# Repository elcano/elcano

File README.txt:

Welcome to the Elcano autonomous tricycle project!
Please see:
http://www.elcanoproject.org/

This repository has been archived. The system consists of several different microprocessors. Elcano/Elcano has been broken into separate repositories for each processor.

To get started, fork and clone the repository:
https://github.com/elcano/elcano

Parameters and settings for each trike are defined in:
/libraries/Settings/Settings.h

Place the contents of the libraries folder into your libraries folder under
Arduino/libraries

The repository includes examples in the file:
Arduino/libraries/Settings/SettingsTemplate.h

Only libraries/Settings/SettingsTemplate.h should be committed in the
repository -- the Arduino/libraries/Settings/Settings.h file is site-specific.

-- Copy
   Arduino/libraries/Settings/SettingsTemplate.h
   to
   Arduino/libraries/Settings/Settings.h
-- Give your trike a different VEHICLE_NUMBER value.
-- Add your own trike's settings, following the examples.
-- Put your settings in a conditional for your new VEHICLE_NUMBER value.

When you pull in updates from the main repository, look for changes in
SettingsTemplate.h and if needed merge them with your own Settings.h.
Especially watch for new trike parameters used in sketches.

Sketches that need these settings should
#include <Settings.h>
*after* all other includes or definitions that are used in Settings.h.

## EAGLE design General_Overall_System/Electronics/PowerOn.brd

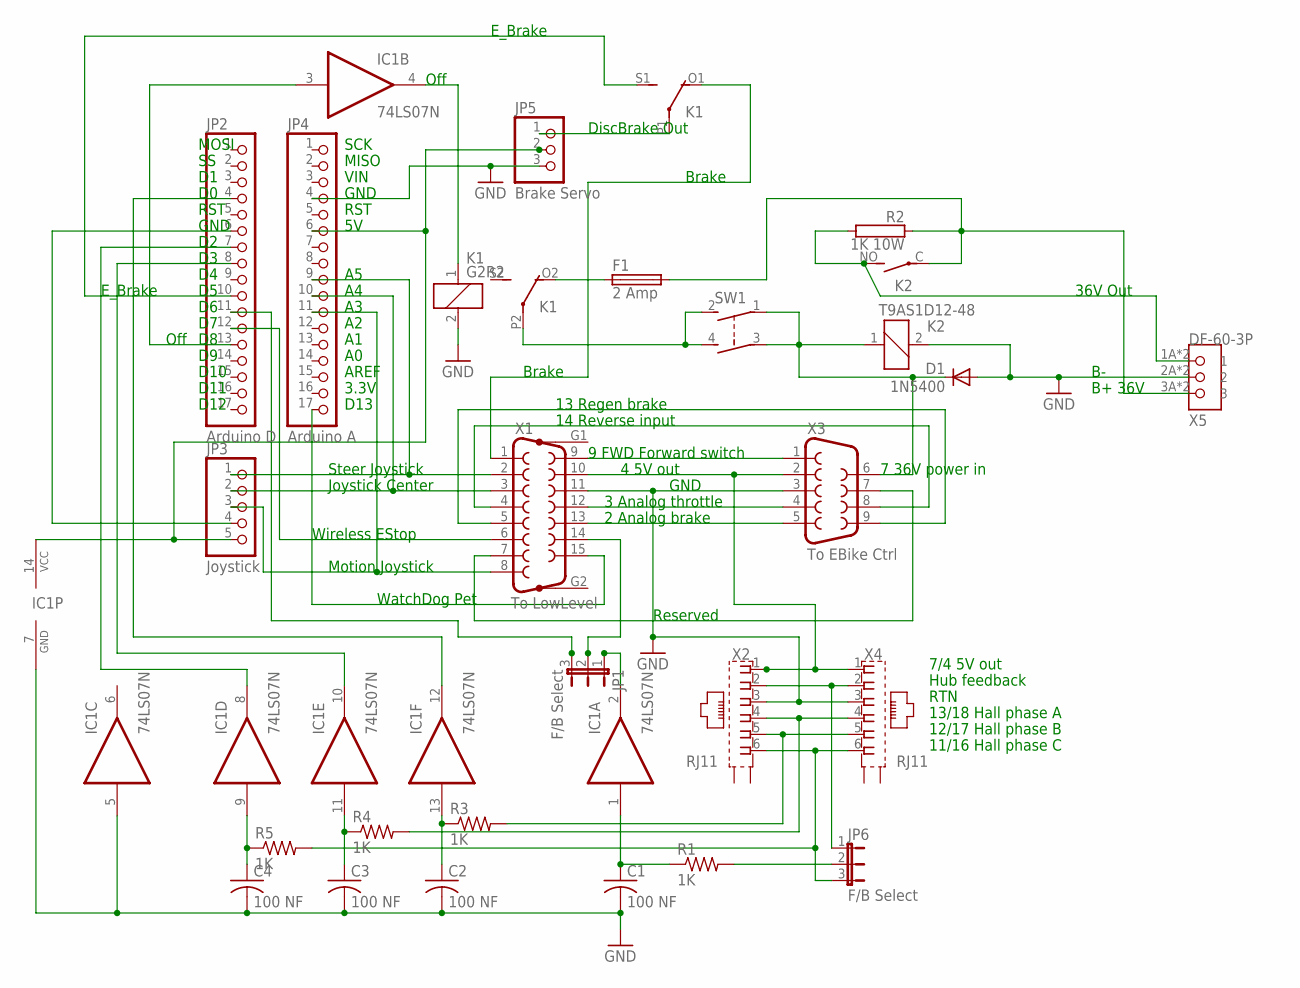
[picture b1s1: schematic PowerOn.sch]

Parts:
C1: 100 NF; C050-050X075
C2, C3, C4: 100 NF; C050-024X044
D1: 1N5400; DO201-15
F1: 2 Amp; SH22,5
IC1: 74LS07N; DIL14
JP1, JP6: F/B Select; JP2
JP2: Arduino D; 1X17
JP3: Joystick; 1X05/90
JP4: Arduino A; 1X17
JP5: Brake Servo; 1X03/90
K1: G2R2
K2: T9AS1D12-48; JT1A-PCB
R1: 1K; 0411/15
R2: 1K 10W; AC07
R3, R4, R5: 1K; 0207/10
SW1: CK-S201
X1: To LowLevel; F15HP
X2, X4: RJ11; XRJK-S-01-6-6-0-2G2-NO
X3: To EBike Ctrl; F09H
X5: HIROSE-DF60-3P-10.16DSA; DF-60-3P-10.16

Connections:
36V_BAT: F1.2, K2.C, R2.1, X5.3A (3), X5.3B (3)
36V_CL: D1.C, K2.1, SW1.1, SW1.3 (P1), X3.6
36V_OUT: K2.NO (S), R2.2, X5.1A (1), X5.1B (1)
36V_SW: K1.P2, SW1.2 (S), SW1.4 (S1)
BRAKE: K1.O1 (O), X1.1
BRK: X1.13, X3.5
BRK_OUT: JP5.1, K1.P1
EBRAKE: JP2.10, K1.S1 (S)
E_RQST: JP2.12, X1.6
F/B: JP1.2, X1.14
FB_SEL: JP6.2, R1.2
FWD: X1.9, X3.1
GND: C1.2, C2.2, C3.2, C4.2, D1.A, IC1.5 (I), IC1.7 (GND), JP4.4, JP5.3, K1.2, K2.2, X1.11, X2.3, X3.3, X4.3, X5.2A (2), X5.2B (2)
GND2: JP2.6, JP3.4
HALLA: R4.2, X2.4, X4.4
HALLB: R3.2, X2.5, X4.5
HALLC: JP6.3, R5.2, X2.6, X4.6
JOY_CEN: JP3.2, JP4.10, X1.3
JOY_MOT: JP3.3, JP4.11, X1.8
JOY_STR: JP3.1, JP4.9, X1.2
LIVE: X1.10, X2.1, X3.2, X4.1
unnamed: IC1.2 (O), JP1.1
unnamed: F1.1, K1.O2 (O)
unnamed: C2.1, IC1.13 (I), R3.1
unnamed: C3.1, IC1.11 (I), R4.1
unnamed: C4.1, IC1.9 (I), R5.1
unnamed: IC1.8 (O), JP2.7
unnamed: IC1.10 (O), JP2.8
unnamed: IC1.12 (O), JP2.4
unnamed: JP1.3, JP2.11
OFF: IC1.3 (I), JP2.13
OFF_DRV: IC1.4 (O), K1.1
RESERVE: X1.7, X3.7
REV: X1.4, X3.8
RGN: X1.5, X3.9
SPD: C1.1, IC1.1 (I), R1.1
SPEED: JP6.1, X2.2, X4.2
THROT: X1.12, X3.4
VCC: IC1.14 (VCC), JP3.5, JP4.6, JP5.2
WDOG: JP4.17, X1.15

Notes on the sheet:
7 36V power in
3 Analog throttle
2 Analog brake
13 Regen brake
14 Reverse input
RTN
13/18 Hall phase A
11/16 Hall phase C
12/17 Hall phase B
7/4 5V out
B+ 36V
Hub feedback
WatchDog Pet
DiscBrake Out
4 5V out
Wireless EStop
Steer Joystick
Joystick Center
Motion Joystick
D12
D11
D10
GND
RST
MOSI
MISO
D13
3.3V
AREF
VIN
SCK
Off
Brake
E_Brake
Reserved
9 FWD Forward switch
36V Out

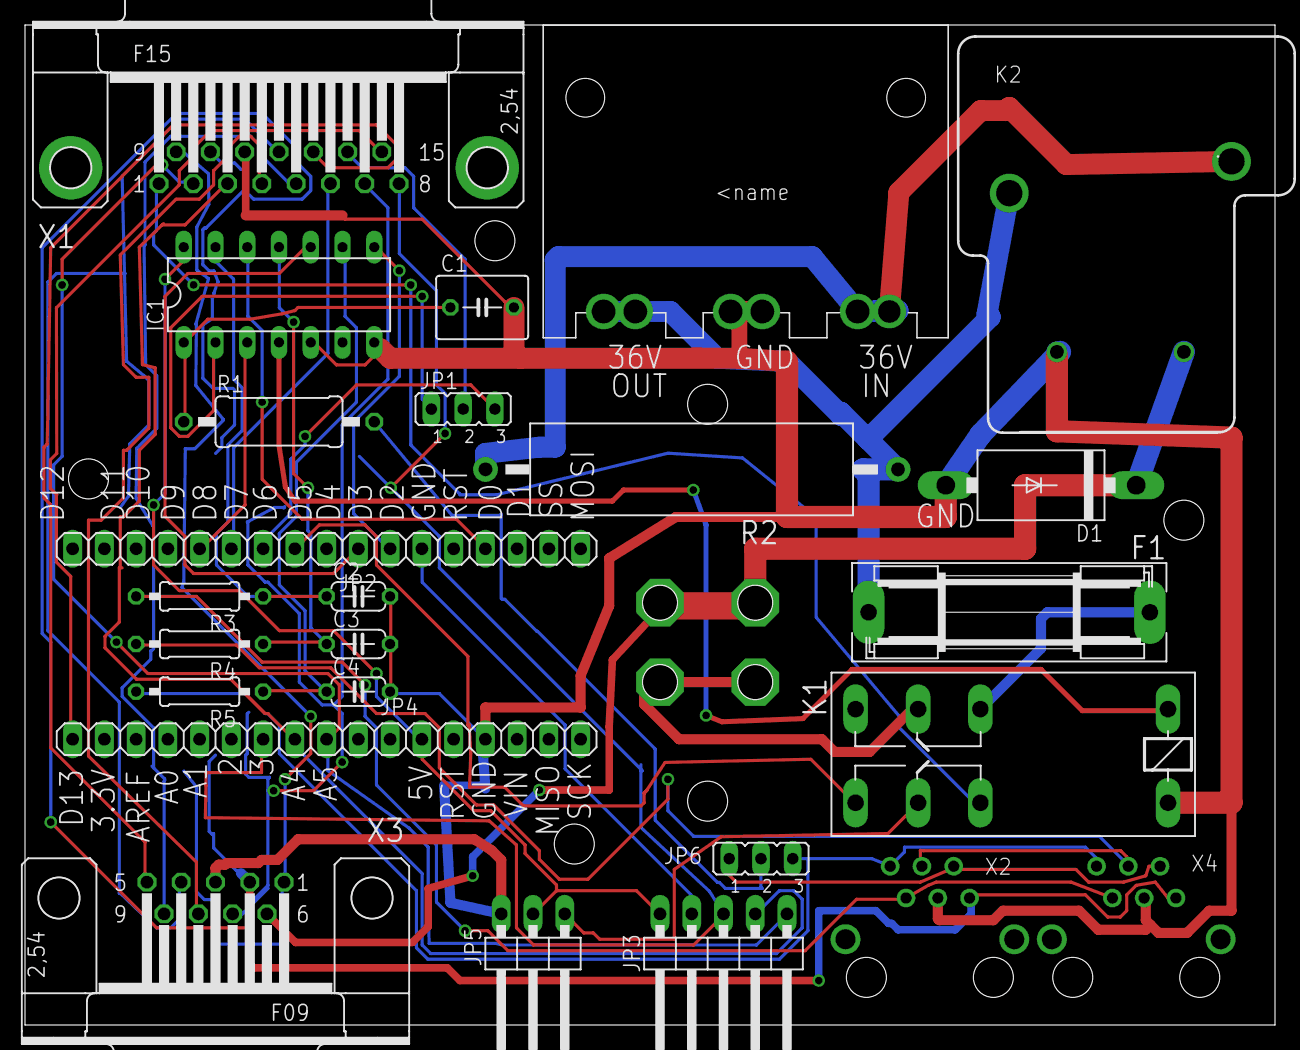
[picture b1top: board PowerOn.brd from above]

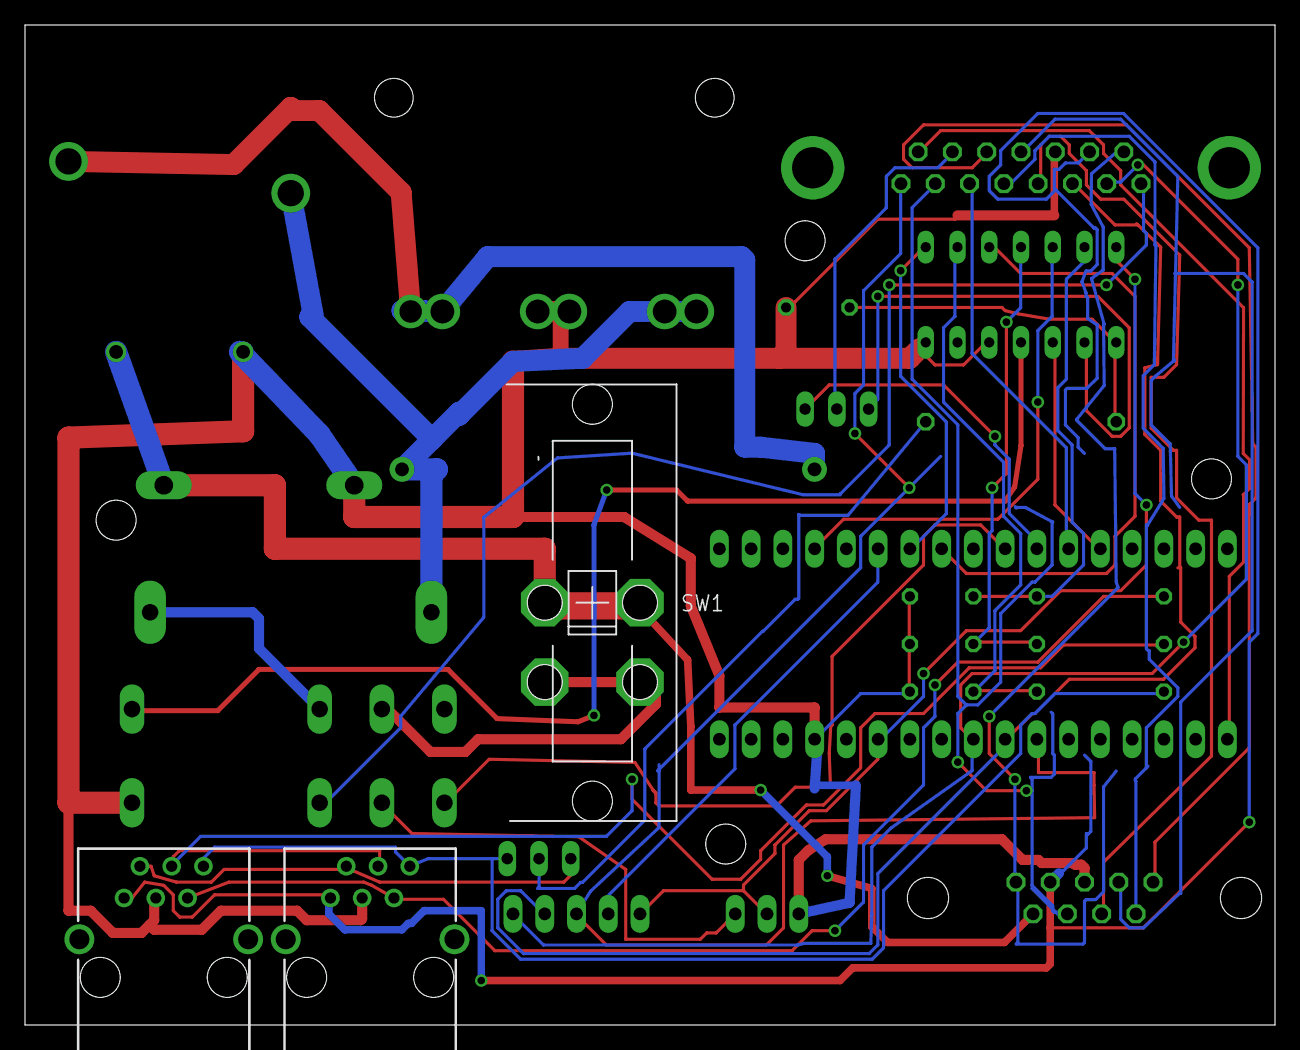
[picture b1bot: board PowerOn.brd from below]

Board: 2 copper layers, 100.0 x 80.0 mm, 26 parts (3 on the bottom side), 40 nets.

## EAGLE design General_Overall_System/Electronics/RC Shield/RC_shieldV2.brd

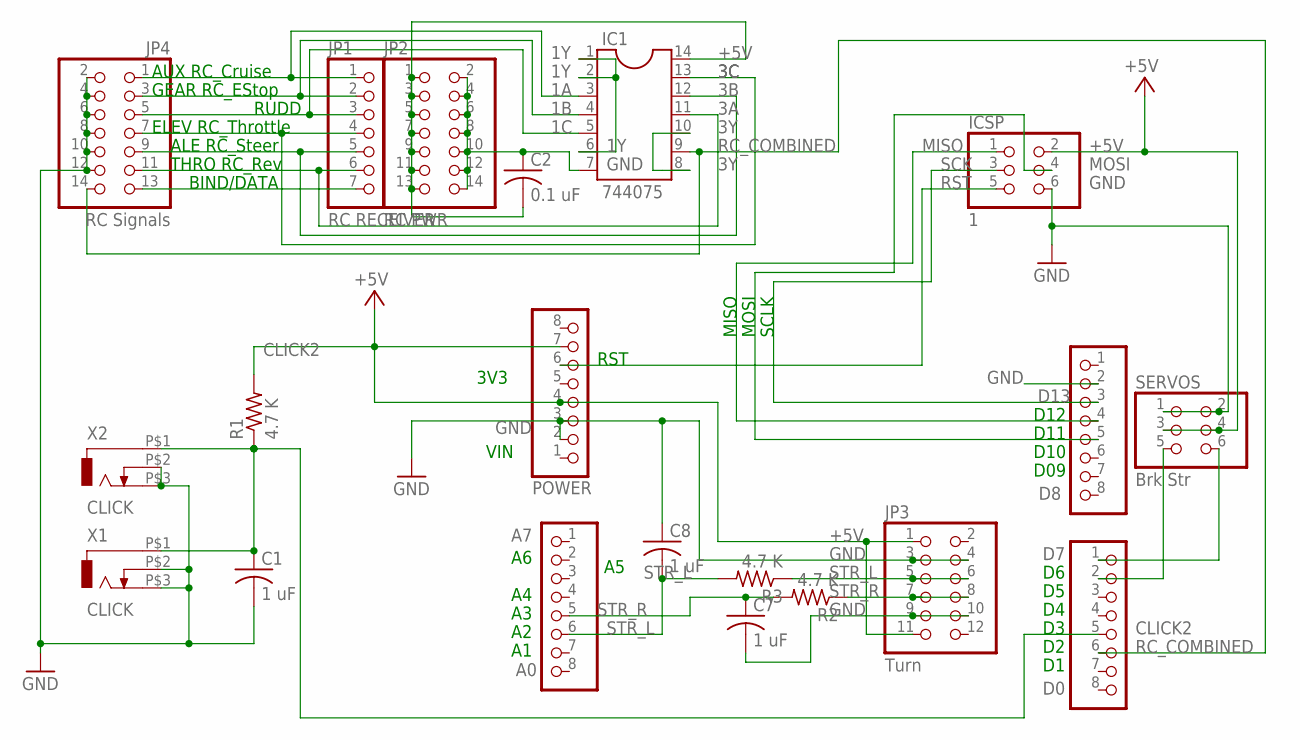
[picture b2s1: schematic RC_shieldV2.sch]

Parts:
A0: A7; 1X08
C1, C7, C8: 1 uF; C025-030X050
C2: 0.1 uF; C025-030X050
D0: D7; 1X08
D8: D13; 1X08
IC1: 744075; DIL14
ICSP: 1; 2X03
JP1: RC RECEIVER; 1X07
JP2: RC PWR; 2X07
JP3: Turn; 2X06
JP4: RC Signals; 2X07
POWER: GND; 1X08
R1, R2, R3: 4.7 K; 0207/10
SERVOS: Brk Str; 2X03
X1, X2: CLICK; ODO_JACK

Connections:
1A: IC1.3, JP1.1, JP4.1
1B: IC1.4, JP1.2, JP4.3
1C: IC1.5, JP1.3, JP4.5
1Y: IC1.1, IC1.2, IC1.6
3A: IC1.11, JP1.6, JP4.11
3B: IC1.12, JP1.5, JP4.9
3C: IC1.13, JP1.4, JP4.7
3Y: IC1.8, IC1.10
+5V: C2.2, IC1.14, ICSP.2, JP2.1, JP2.3, JP2.5, JP2.7, JP2.9, JP2.11, JP2.13, JP3.1, JP3.11, POWER.4, POWER.7, R1.2, SERVOS.3, SERVOS.4
CLICK2: C1.1, D0.5, R1.1, X1.P$1 (1), X2.P$1 (1)
GND: C1.2, C2.1, C7.2, C8.1, D8.2, IC1.7, ICSP.6, JP2.2, JP2.4, JP2.6, JP2.8, JP2.10, JP2.12, JP2.14, JP3.3, JP3.4, JP3.9, JP3.10, JP4.2, JP4.4, JP4.6, JP4.8, JP4.10, JP4.12, POWER.2, POWER.3, SERVOS.1, SERVOS.2, X1.P$2 (2), X1.P$3 (3), X2.P$2 (2), X2.P$3 (3)
MISO: D8.4, ICSP.1
MOSI: D8.5, ICSP.4
unnamed: JP3.7, JP3.8, R2.1
unnamed: JP3.5, JP3.6, R3.1
unnamed: JP1.7, JP4.13
unnamed: D0.2, SERVOS.5
unnamed: D0.1, SERVOS.6
RC_COMBINED: D0.6, IC1.9, JP4.14
RST: ICSP.5, POWER.6
SCK: D8.3, ICSP.3
STR_L: A0.6, C8.2, R3.2
STR_R: A0.5, C7.1, R2.2

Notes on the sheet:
D10
D11
D12
D09
VIN
MISO
MOSI
SCLK
RST
3V3
AUX RC_Cruise
GEAR RC_EStop
RUDD
ELEV RC_Throttle
ALE RC_Steer
THRO RC_Rev
BIND/DATA

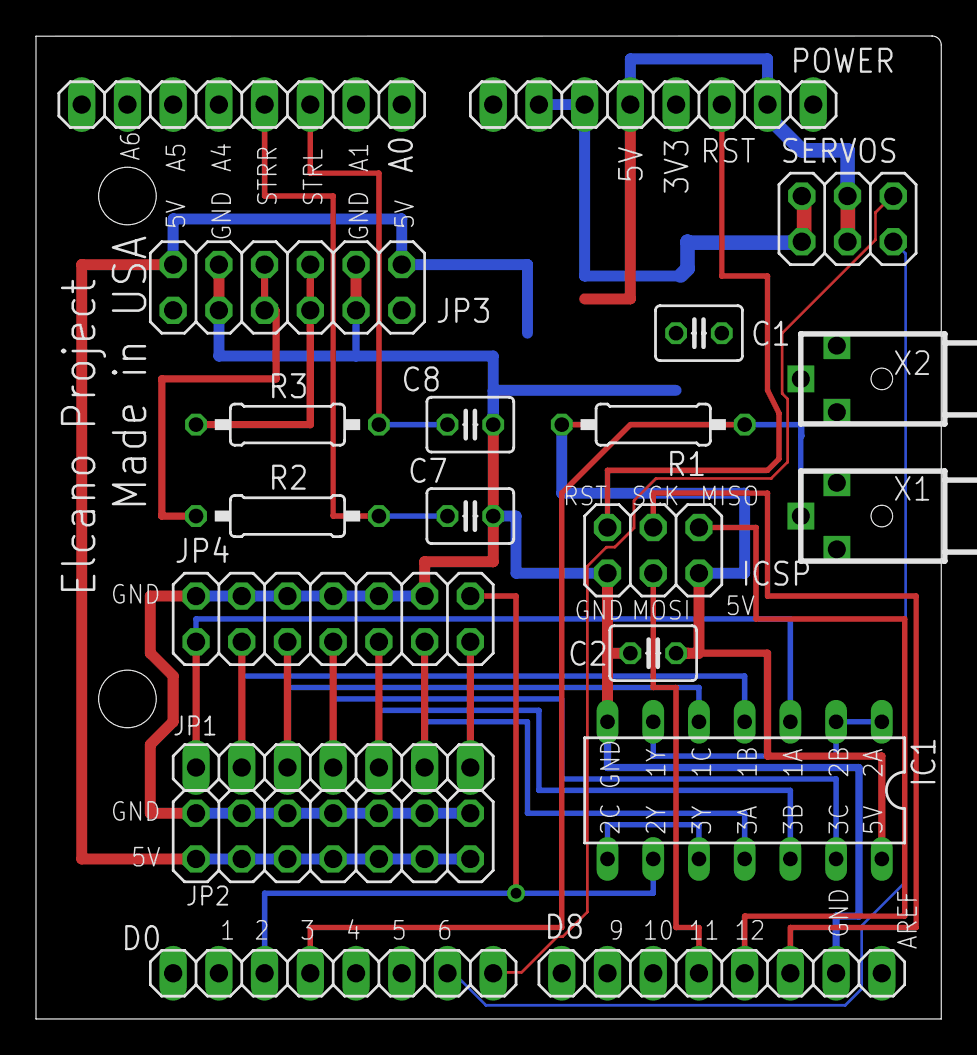
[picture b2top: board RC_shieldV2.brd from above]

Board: 2 copper layers, 50.3 x 54.6 mm, 20 parts (0 on the bottom side), 23 nets.

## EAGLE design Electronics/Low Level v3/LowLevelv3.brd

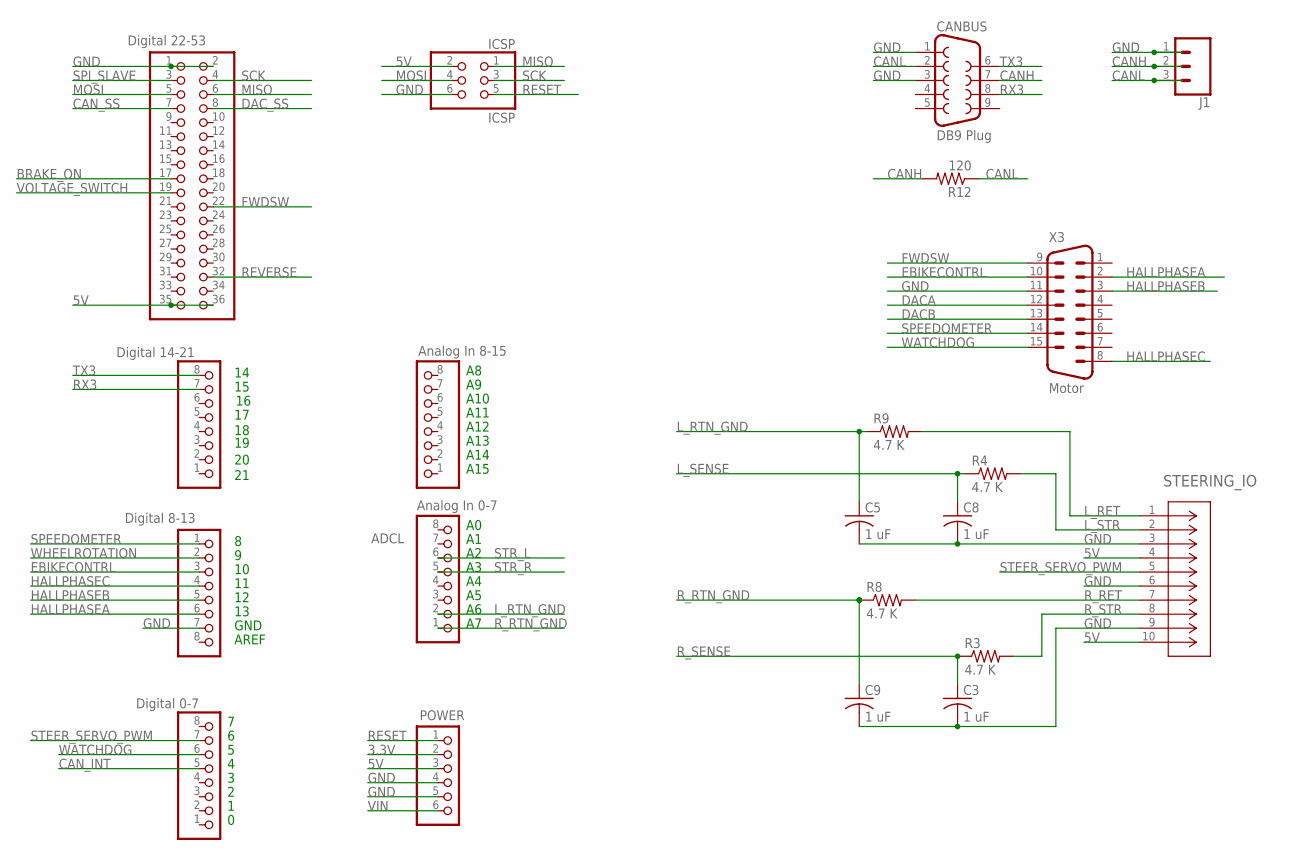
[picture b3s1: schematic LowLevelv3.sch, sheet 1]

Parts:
ADCH: Analog In 8-15; 1X08
ADCL: Analog In 0-7; 1X08
C3, C5, C8, C9: 1 uF; C1206
CANBUS: DB9 Plug; DB9
DIGITAL_0-7: Digital 0-7; 1X08
DIGITAL_8-13: Digital 8-13; 1X08
DIGITAL_14-21: Digital 14-21; 1X08
ICSP: ICSP; 2X03
J1: CONN_03-SCREW-5MM; SCREWTERMINAL-5MM-3
MEGA_EXPANSION: Digital 22-53; PINHEAD_2X18
POWER: PINHD-1X6; 1X06
R3, R4, R8, R9: 4.7 K; R1206
R12: 120; R1206
STEERING_IO: 5-104069-4; CONN_5-104069-4_TYCO
X3: Motor; 182-015-MALE

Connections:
3.3V: POWER.2
5V: ICSP.2, MEGA_EXPANSION.35, MEGA_EXPANSION.36, POWER.3, STEERING_IO.4, STEERING_IO.10; also elsewhere on the board
BRAKE_ON: MEGA_EXPANSION.17; also elsewhere on the board
CANH: CANBUS.7, J1.2, R12.2; also elsewhere on the board
CANL: CANBUS.2, J1.3, R12.1; also elsewhere on the board
CAN_INT: DIGITAL_0-7.5; also elsewhere on the board
CAN_SS: MEGA_EXPANSION.7; also elsewhere on the board
DACA: X3.12; also elsewhere on the board
DACB: X3.13; also elsewhere on the board
DAC_SS: MEGA_EXPANSION.8; also elsewhere on the board
EBIKECONTRL: DIGITAL_8-13.3, X3.10
FWDSW: MEGA_EXPANSION.22, X3.9
GND: C3.2, C5.2, C8.2, C9.2, CANBUS.1, CANBUS.3, DIGITAL_8-13.7, ICSP.6, J1.1, MEGA_EXPANSION.1, MEGA_EXPANSION.2, POWER.4, POWER.5, STEERING_IO.3, STEERING_IO.6, STEERING_IO.9, X3.11; also elsewhere on the board
HALLPHASEA: DIGITAL_8-13.6, X3.2
HALLPHASEB: DIGITAL_8-13.5, X3.3
HALLPHASEC: DIGITAL_8-13.4, X3.8
L_RET: R9.2, STEERING_IO.1
L_RTN_GND: ADCL.2, C5.1, R9.1
L_SENSE: C8.1, R4.1
L_STR: R4.2, STEERING_IO.2
MISO: ICSP.1, MEGA_EXPANSION.6; also elsewhere on the board
MOSI: ICSP.4, MEGA_EXPANSION.5; also elsewhere on the board
RESET: ICSP.5, POWER.1; also elsewhere on the board
REVERSE: MEGA_EXPANSION.32
RX3: CANBUS.8, DIGITAL_14-21.7
R_RET: R8.2, STEERING_IO.7
R_RTN_GND: ADCL.1, C9.1, R8.1
R_SENSE: C3.1, R3.1
R_STR: R3.2, STEERING_IO.8
SCK: ICSP.3, MEGA_EXPANSION.4; also elsewhere on the board
SPEEDOMETER: DIGITAL_8-13.1, X3.14
SPI_SLAVE: MEGA_EXPANSION.3
STEER_SERVO_PWM: DIGITAL_0-7.7, STEERING_IO.5
STR_L: ADCL.6
STR_R: ADCL.5
TX3: CANBUS.6, DIGITAL_14-21.8
VIN: POWER.6
VOLTAGE_SWITCH: MEGA_EXPANSION.19; also elsewhere on the board
WATCHDOG: DIGITAL_0-7.6, X3.15
WHEELROTATION: DIGITAL_8-13.2; also elsewhere on the board

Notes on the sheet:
A10
A11
A12
A13
A14
A15
GND
AREF

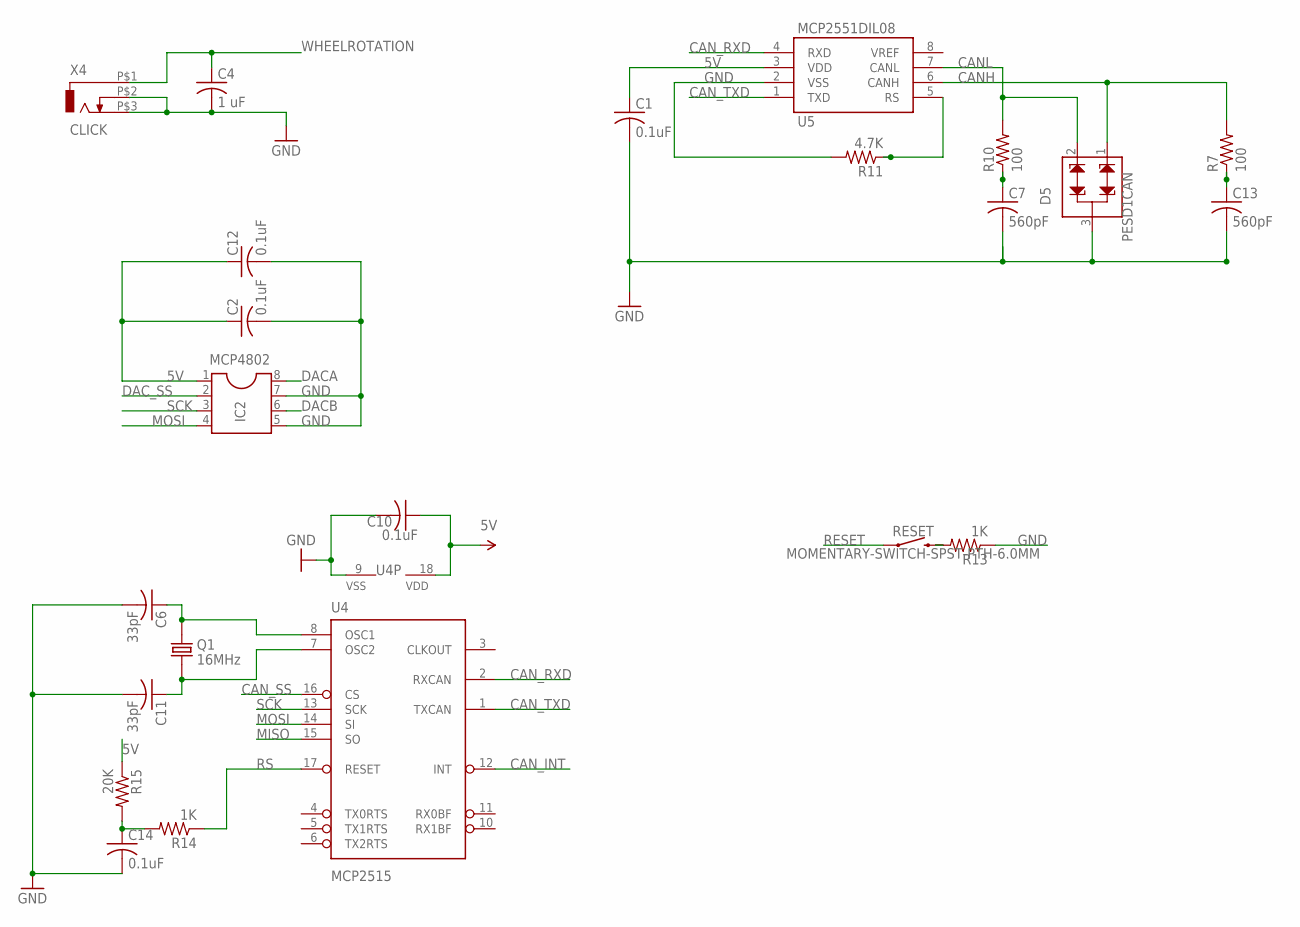
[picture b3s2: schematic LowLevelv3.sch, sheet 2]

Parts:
C1, C2, C10, C12, C14: 0.1uF; C1206
C4: 1 uF; C1206
C6, C11: 33pF; C1206
C7, C13: 560pF; C1206
D5: PESD1CAN; SPARKFUN-DISCRETESEMI_SOT23-3
IC2: MCP4802; DIL08
Q1: 16MHz; XTAL_ECS-160-20-46X
R7, R10: 100; R1206
R11: 4.7K; R1206
R13, R14: 1K; R1206
R15: 20K; R1206
RESET: MOMENTARY-SWITCH-SPST-PTH-6.0MM; TACTILE_SWITCH_PTH_6.0MM
U4: MCP2515; DIP18
U5: MCP2551DIL08; IC-PACKAGE_DIL08
X4: CLICK; ODO_JACK

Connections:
5V: C1.1, C2.1, C10.1, C12.1, IC2.1, R15.1, U4.18 (VDD), U5.3 (VDD); also elsewhere on the board
CANH: D5.1, R7.2, U5.6 (CANH); also elsewhere on the board
CANL: D5.2, R10.2, U5.7 (CANL); also elsewhere on the board
CAN_INT: U4.12 (INT); also elsewhere on the board
CAN_RXD: U4.2 (RXCAN), U5.4 (RXD)
CAN_SS: U4.16 (CS); also elsewhere on the board
CAN_TXD: U4.1 (TXCAN), U5.1 (TXD)
DACA: IC2.8; also elsewhere on the board
DACB: IC2.6; also elsewhere on the board
DAC_SS: IC2.2; also elsewhere on the board
GND: C1.2, C2.2, C4.2, C6.2, C7.2, C10.2, C11.2, C12.2, C13.2, C14.2, D5.3, IC2.5, IC2.7, R11.2, R13.1, U4.9 (VSS), U5.2 (VSS), X4.P$2 (2), X4.P$3 (3); also elsewhere on the board
MISO: U4.15 (SO); also elsewhere on the board
MOSI: IC2.4, U4.14 (SI); also elsewhere on the board
unnamed: R13.2, RESET.3 (2)
unnamed: C14.1, R14.2, R15.2
unnamed: C7.1, R10.1
unnamed: C13.1, R7.1
unnamed: R11.1, U5.5 (RS)
unnamed: C6.1, Q1.2, U4.8 (OSC1)
unnamed: C11.1, Q1.1, U4.7 (OSC2)
RESET: RESET.1; also elsewhere on the board
RS: R14.1, U4.17 (RESET)
SCK: IC2.3, U4.13 (SCK); also elsewhere on the board
WHEELROTATION: C4.1, X4.P$1 (1); also elsewhere on the board

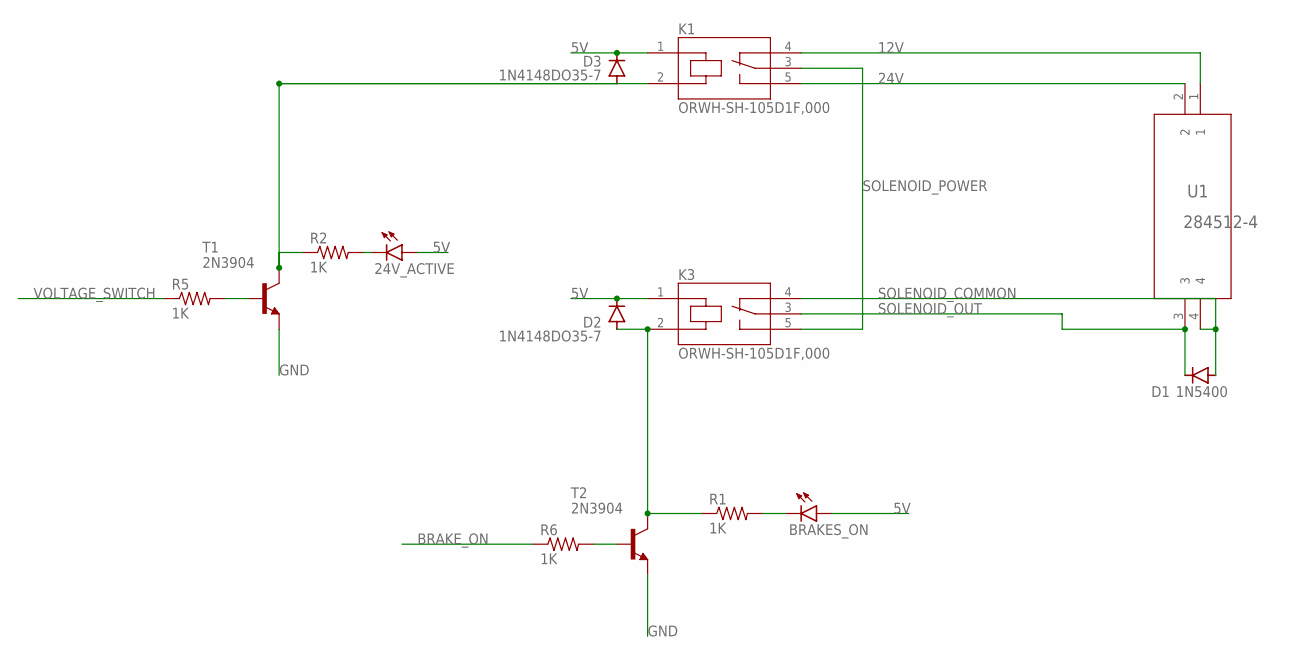
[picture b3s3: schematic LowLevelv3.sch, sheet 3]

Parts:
24V_ACTIVE: LED3MM
BRAKES_ON: LED3MM
D1: 1N5400; DO201-15
D2, D3: 1N4148DO35-7; DO35-7
K1, K3: ORWH-SH-105D1F,000; TE_ORWH-SH-105D1F,000
R1, R2, R5, R6: 1K; R1206
T1, T2: 2N3904; TO92
U1: 284512-4

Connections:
5V: 24V_ACTIVE.A, BRAKES_ON.A, D2.C, D3.C, K1.1 (C1), K3.1 (C1); also elsewhere on the board
12V: K1.4 (NC), U1.1
24V: K1.5 (NO), U1.2
BRAKE_ON: R6.1; also elsewhere on the board
GND: T1.3 (E), T2.3 (E); also elsewhere on the board
unnamed: R5.2, T1.2 (B)
unnamed: D3.A, K1.2 (C2), R2.1, T1.1 (C)
unnamed: 24V_ACTIVE.K (C), R2.2
unnamed: R6.2, T2.2 (B)
unnamed: D2.A, K3.2 (C2), R1.1, T2.1 (C)
unnamed: BRAKES_ON.K (C), R1.2
SOLENOID_COMMON: D1.A, K3.4 (NC), U1.4
SOLENOID_OUT: D1.C, K3.3 (C), U1.3
SOLENOID_POWER: K1.3 (C), K3.5 (NO)
VOLTAGE_SWITCH: R5.1; also elsewhere on the board

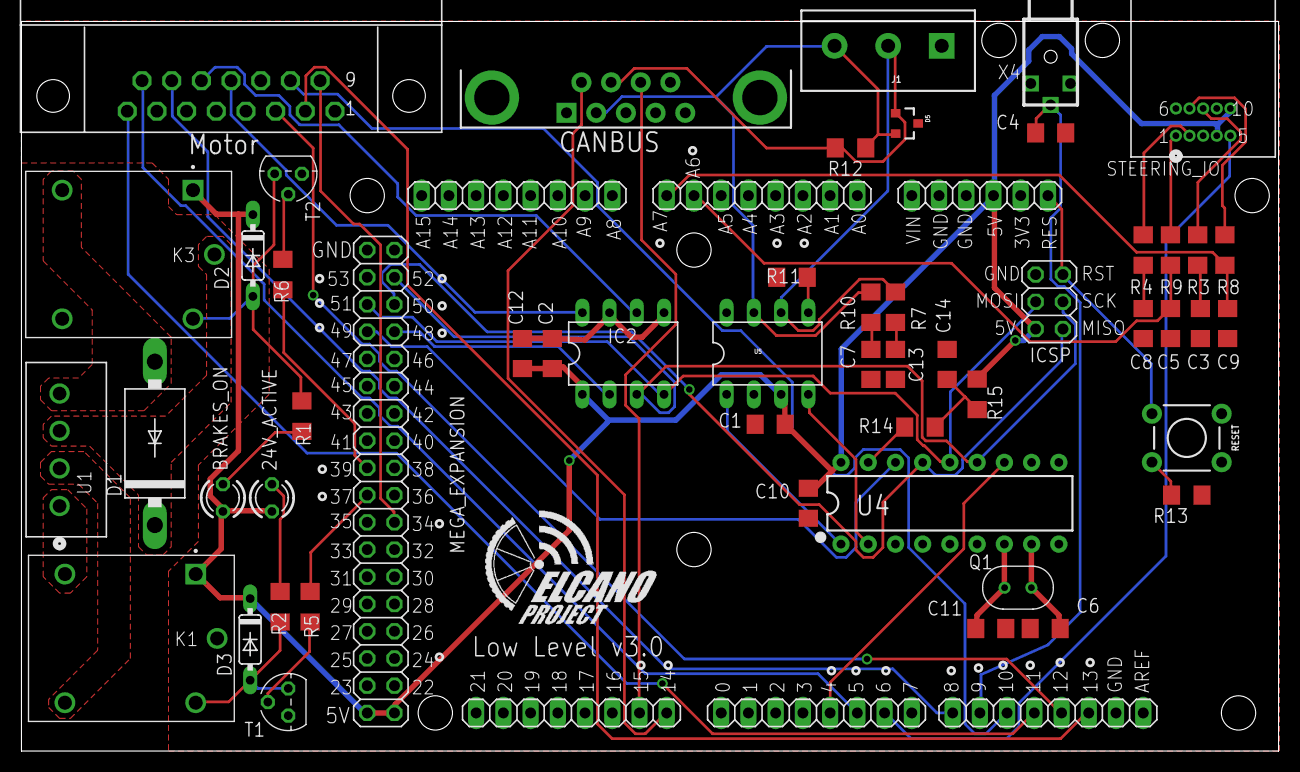
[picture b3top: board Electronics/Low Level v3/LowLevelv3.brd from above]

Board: 2 copper layers, 117.3 x 68.1 mm, 58 parts (0 on the bottom side), 55 nets.

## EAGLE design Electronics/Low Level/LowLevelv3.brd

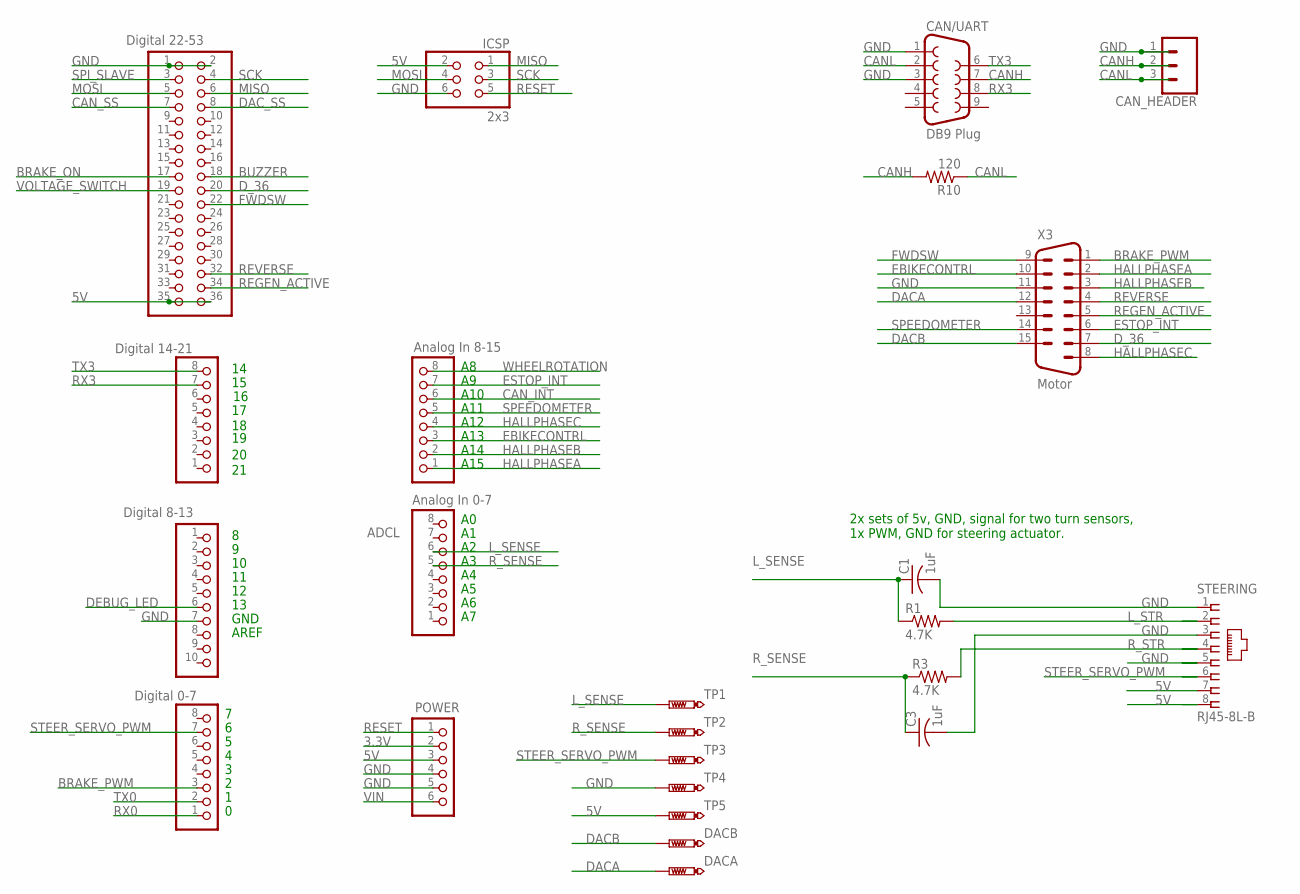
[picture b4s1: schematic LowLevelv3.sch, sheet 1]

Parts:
ADCH: Analog In 8-15; 1X08
ADCL: Analog In 0-7; 1X08
C1, C3: 1uF; C1206
CAN/UART: DB9 Plug; DB9
CAN_HEADER: CONN_03-SCREW-5MM; SCREWTERMINAL-5MM-3
DACA: PTR1PAD1-17; P1-17
DACB: PTR1PAD1-17; P1-17
DIGITAL_0-7: Digital 0-7; 1X08
DIGITAL_8-13: Digital 8-13; 1X10
DIGITAL_14-21: Digital 14-21; 1X08
ICSP: 2x3; 2X03
MEGA_EXPANSION: Digital 22-53; PINHEAD_2X18
POWER: PINHD-1X6; 1X06
R1, R3: 4.7K; R1206
R10: 120; R1206
STEERING: RJ45-8L-B; RJ45-NO-SHIELD
TP1, TP2, TP3, TP4, TP5: PTR1PAD1-17; P1-17
X3: Motor; 182-015-MALE

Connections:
3.3V: POWER.2
5V: ICSP.2, MEGA_EXPANSION.35, MEGA_EXPANSION.36, POWER.3, STEERING.7, STEERING.8, TP5.TP; also elsewhere on the board
BRAKE_ON: MEGA_EXPANSION.17; also elsewhere on the board
BRAKE_PWM: DIGITAL_0-7.3, X3.1
BUZZER: MEGA_EXPANSION.18; also elsewhere on the board
CANH: CAN/UART.7, CAN_HEADER.2, R10.2; also elsewhere on the board
CANL: CAN/UART.2, CAN_HEADER.3, R10.1; also elsewhere on the board
CAN_INT: ADCH.6; also elsewhere on the board
CAN_SS: MEGA_EXPANSION.7; also elsewhere on the board
DACA: DACA.TP, X3.12; also elsewhere on the board
DACB: DACB.TP, X3.15; also elsewhere on the board
DAC_SS: MEGA_EXPANSION.8; also elsewhere on the board
DEBUG_LED: DIGITAL_8-13.6; also elsewhere on the board
D_36: MEGA_EXPANSION.20, X3.7
EBIKECONTRL: ADCH.3, X3.10
ESTOP_INT: ADCH.7, X3.6; also elsewhere on the board
FWDSW: MEGA_EXPANSION.22, X3.9
GND: C1.2, C3.2, CAN/UART.1, CAN/UART.3, CAN_HEADER.1, DIGITAL_8-13.7, ICSP.6, MEGA_EXPANSION.1, MEGA_EXPANSION.2, POWER.4, POWER.5, STEERING.1, STEERING.3, STEERING.5, TP4.TP, X3.11; also elsewhere on the board
HALLPHASEA: ADCH.1, X3.2
HALLPHASEB: ADCH.2, X3.3
HALLPHASEC: ADCH.4, X3.8
L_SENSE: ADCL.6, C1.1, R1.1, TP1.TP
L_STR: R1.2, STEERING.2
MISO: ICSP.1, MEGA_EXPANSION.6; also elsewhere on the board
MOSI: ICSP.4, MEGA_EXPANSION.5; also elsewhere on the board
REGEN_ACTIVE: MEGA_EXPANSION.34, X3.5
RESET: ICSP.5, POWER.1; also elsewhere on the board
REVERSE: MEGA_EXPANSION.32, X3.4
RX0: DIGITAL_0-7.1
RX3: CAN/UART.8, DIGITAL_14-21.7
R_SENSE: ADCL.5, C3.1, R3.1, TP2.TP
R_STR: R3.2, STEERING.4
SCK: ICSP.3, MEGA_EXPANSION.4; also elsewhere on the board
SPEEDOMETER: ADCH.5, X3.14
SPI_SLAVE: MEGA_EXPANSION.3
STEER_SERVO_PWM: DIGITAL_0-7.7, STEERING.6, TP3.TP
TX0: DIGITAL_0-7.2
TX3: CAN/UART.6, DIGITAL_14-21.8
VIN: POWER.6
VOLTAGE_SWITCH: MEGA_EXPANSION.19; also elsewhere on the board
WHEELROTATION: ADCH.8; also elsewhere on the board

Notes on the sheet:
A10
A11
A12
A13
A14
A15
GND
AREF
2x sets of 5v, GND, signal for two turn sensors, 1x PWM, GND for steering actuator.

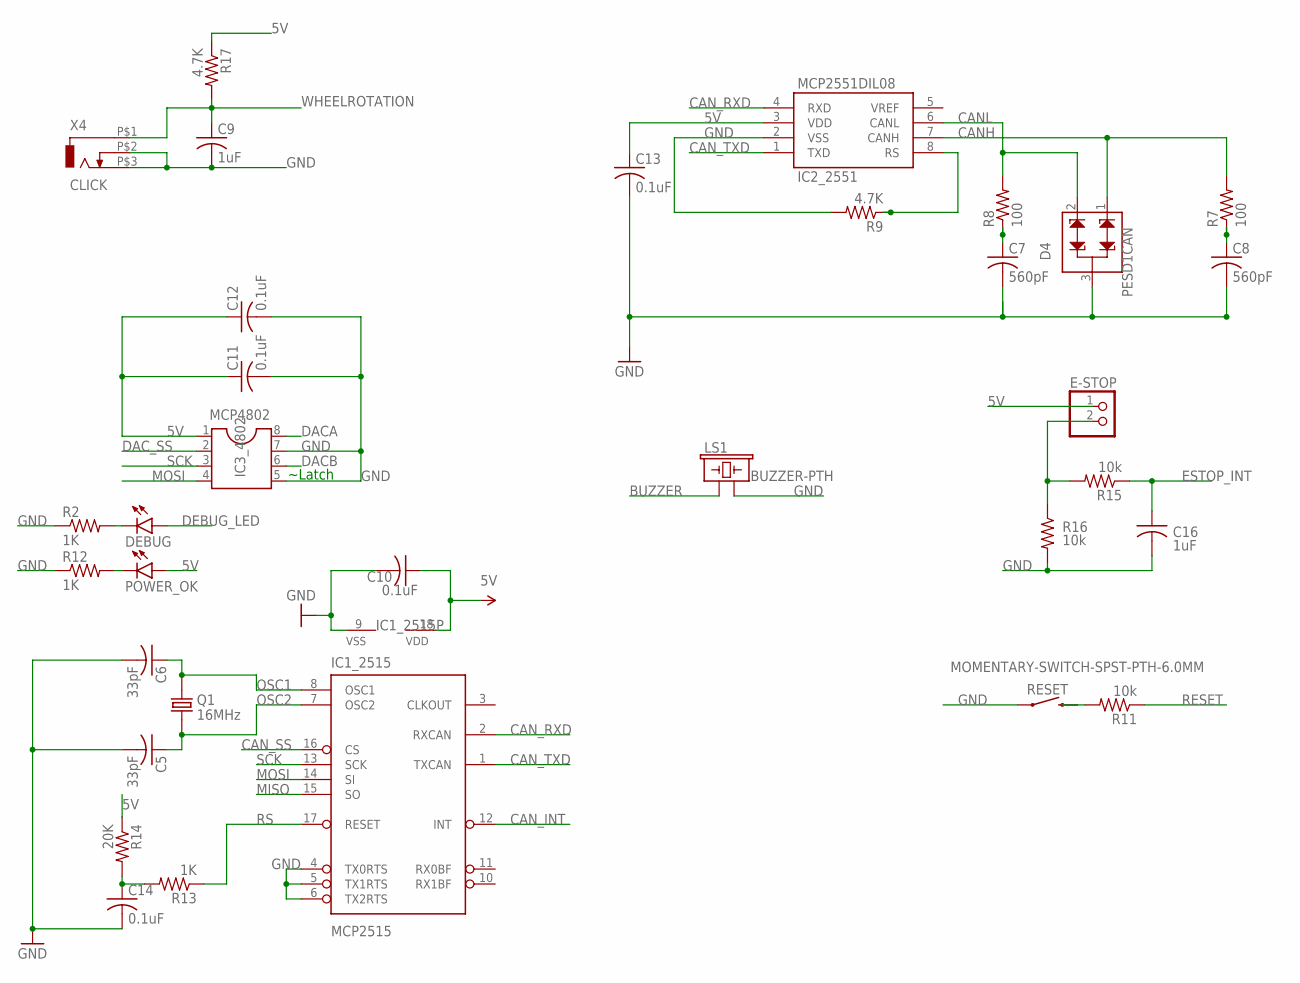
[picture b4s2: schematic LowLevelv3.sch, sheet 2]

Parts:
C5, C6: 33pF; C1206
C7, C8: 560pF; C1206
C9, C16: 1uF; C1206
C10, C11, C12, C13, C14: 0.1uF; C1206
D4: PESD1CAN; SPARKFUN-DISCRETESEMI_SOT23-3
DEBUG: LED3MM
E-STOP: PINHD-1X2; 1X02
IC1_2515: MCP2515; DIP18
IC2_2551: MCP2551DIL08; IC-PACKAGE_DIL08
IC3_4802: MCP4802; DIL08
LS1: BUZZER-PTH; BUZZER-12MM
POWER_OK: LED3MM
Q1: 16MHz; XTAL_ECS-160-20-46X
R2, R12, R13: 1K; R1206
R7, R8: 100; R1206
R9, R17: 4.7K; R1206
R11, R15, R16: 10k; R1206
R14: 20K; R1206
RESET: MOMENTARY-SWITCH-SPST-PTH-6.0MM; TACTILE_SWITCH_PTH_6.0MM
X4: CLICK; ODO_JACK

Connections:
5V: C10.1, C11.1, C12.1, C13.1, E-STOP.1, IC1_2515.18 (VDD), IC2_2551.3 (VDD), IC3_4802.1, POWER_OK.A, R14.1, R17.1; also elsewhere on the board
BUZZER: LS1.+ (1); also elsewhere on the board
CANH: D4.1, IC2_2551.7 (CANH), R7.2; also elsewhere on the board
CANL: D4.2, IC2_2551.6 (CANL), R8.2; also elsewhere on the board
CAN_INT: IC1_2515.12 (INT); also elsewhere on the board
CAN_RXD: IC1_2515.2 (RXCAN), IC2_2551.4 (RXD)
CAN_SS: IC1_2515.16 (CS); also elsewhere on the board
CAN_TXD: IC1_2515.1 (TXCAN), IC2_2551.1 (TXD)
DACA: IC3_4802.8; also elsewhere on the board
DACB: IC3_4802.6; also elsewhere on the board
DAC_SS: IC3_4802.2; also elsewhere on the board
DEBUG_LED: DEBUG.A; also elsewhere on the board
ESTOP_INT: C16.1, R15.1; also elsewhere on the board
GND: C5.2, C6.2, C7.2, C8.2, C9.2, C10.2, C11.2, C12.2, C13.2, C14.2, C16.2, D4.3, IC1_2515.4 (TX0RTS), IC1_2515.5 (TX1RTS), IC1_2515.6 (TX2RTS), IC1_2515.9 (VSS), IC2_2551.2 (VSS), IC3_4802.5, IC3_4802.7, LS1.- (2), R2.1, R9.2, R12.1, R16.2, RESET.1, X4.P$2 (2), X4.P$3 (3); also elsewhere on the board
MISO: IC1_2515.15 (SO); also elsewhere on the board
MOSI: IC1_2515.14 (SI), IC3_4802.4; also elsewhere on the board
unnamed: R11.2, RESET.3 (2)
unnamed: C14.1, R13.2, R14.2
unnamed: DEBUG.K (C), R2.2
unnamed: E-STOP.2, R15.2, R16.1
unnamed: C7.1, R8.1
unnamed: C8.1, R7.1
unnamed: POWER_OK.K (C), R12.2
unnamed: IC2_2551.8 (RS), R9.1
OSC1: C6.1, IC1_2515.8 (OSC1), Q1.2
OSC2: C5.1, IC1_2515.7 (OSC2), Q1.1
RESET: R11.1; also elsewhere on the board
RS: IC1_2515.17 (RESET), R13.1
SCK: IC1_2515.13 (SCK), IC3_4802.3; also elsewhere on the board
WHEELROTATION: C9.1, R17.2, X4.P$1 (1); also elsewhere on the board

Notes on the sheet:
~Latch

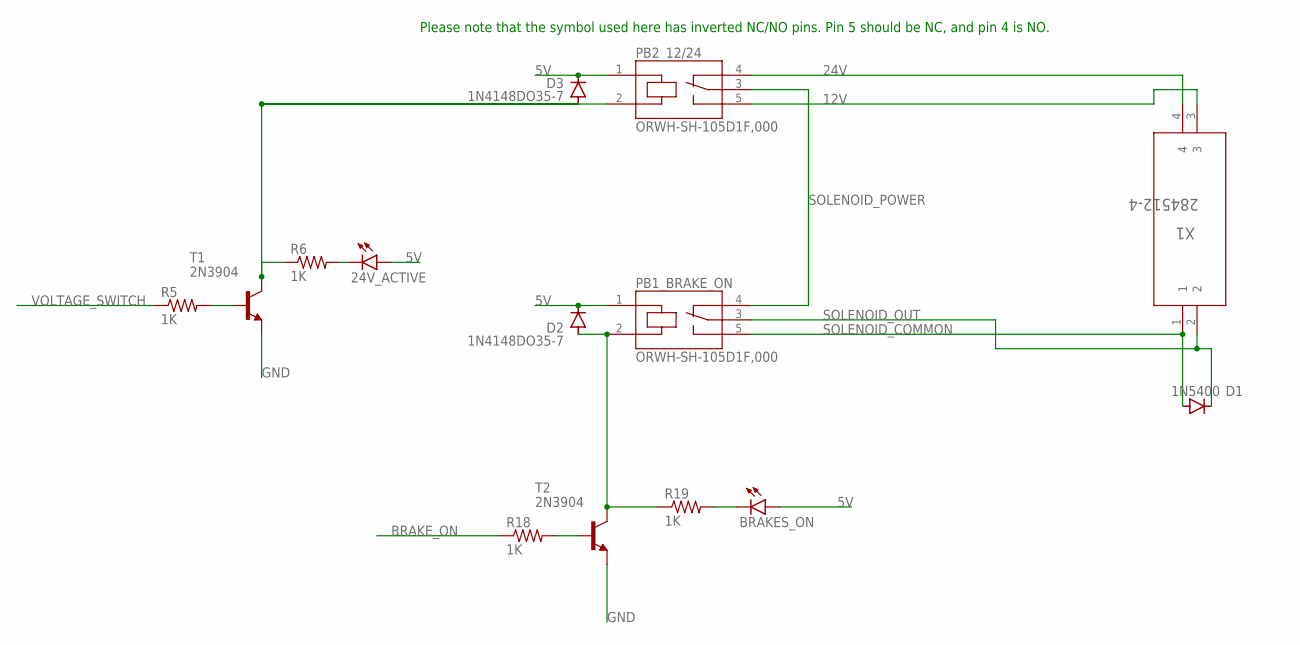
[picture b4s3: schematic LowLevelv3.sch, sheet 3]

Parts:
24V_ACTIVE: LED3MM
BRAKES_ON: LED3MM
D1: 1N5400; DO201-15
D2, D3: 1N4148DO35-7; DO35-7
PB1_BRAKE_ON, PB2_12/24: ORWH-SH-105D1F,000; TE_ORWH-SH-105D1F,000
R5, R6, R18, R19: 1K; R1206
T1, T2: 2N3904; TO92
X1: 284512-4

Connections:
5V: 24V_ACTIVE.A, BRAKES_ON.A, D2.C, D3.C, PB1_BRAKE_ON.1 (C1), PB2_12/24.1 (C1); also elsewhere on the board
12V: PB2_12/24.5 (NO), X1.3
24V: PB2_12/24.4 (NC), X1.4
BRAKE_ON: R18.1; also elsewhere on the board
GND: T1.3 (E), T2.3 (E); also elsewhere on the board
unnamed: R5.2, T1.2 (B)
unnamed: D3.A, PB2_12/24.2 (C2), R6.1, T1.1 (C)
unnamed: 24V_ACTIVE.K (C), R6.2
unnamed: R18.2, T2.2 (B)
unnamed: D2.A, PB1_BRAKE_ON.2 (C2), R19.1, T2.1 (C)
unnamed: BRAKES_ON.K (C), R19.2
SOLENOID_COMMON: D1.A, PB1_BRAKE_ON.5 (NO), X1.1
SOLENOID_OUT: D1.C, PB1_BRAKE_ON.3 (C), X1.2
SOLENOID_POWER: PB1_BRAKE_ON.4 (NC), PB2_12/24.3 (C)
VOLTAGE_SWITCH: R5.1; also elsewhere on the board

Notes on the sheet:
Please note that the symbol used here has inverted NC/NO pins. Pin 5 should be NC, and pin 4 is NO.

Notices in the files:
parts and their libraries:
SparkFun-Connectors: Licensing: Creative Commons ShareAlike 4.0 International - https://creativecommons.org/licenses/by-sa/4.0
SparkFun-Connectors: Licensing: CC v3.0 Share-Alike You are welcome to use this library for commercial purposes.
